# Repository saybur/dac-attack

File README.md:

DAC Attack!
===========

A small [S/PDIF](https://en.wikipedia.org/wiki/S/PDIF) to
[line-level](https://en.wikipedia.org/wiki/Line_level) audio adapter design.
The intended use case is with some versions of
[ZuluSCSI](https://zuluscsi.com/), though the design should work with any
S/PDIF compatible output source generating a TTL-compatible signal.

Used with a compatible board, and the appropriate firmware, this allows sending
audio to a retro computer. See later sections for usage information.

As of this writing, only some ZuluSCSI variants offer audio output. This list
may change in the future. Refer to the ZuluSCSI project page for details about
audio output support.

License and Disclaimer
----------------------

This project is made available under the CERN Open Hardware Licence
strongly-reciprocal variant version 2, available at [LICENSE](LICENSE).

This source is distributed WITHOUT ANY EXPRESS OR IMPLIED WARRANTY, INCLUDING
OF MERCHANTABILITY, SATISFACTORY QUALITY AND FITNESS FOR A PARTICULAR PURPOSE.
Please see the CERN-OHL-S v2 for applicable conditions.

ZuluSCSI&trade; is a registered trademark of Rabbit Hole Computing&trade;, used
with permission.

Assembly
--------

The author has had JLCPCB assemble these boards as prototypes. The files
`dac-attack-bom.csv` and `dac-attack-top-pos.csv` files were used successfully,
though caution should still be excercised: other open-source hardware projects
have reported some inconsistency in individual orders using files like these.

Adding through-hole components to assembled boards is relatively
straightforward. The choice of what connectors to solder is up to the user:

- 'analog' provides standard line-level output for sending to a sound card.
- 'digital' provides TTL-level S/PDIF from the CS8416 chip, which should
  _theoretically_ be suitable for sending to a sound card with a digital-in
  connector, ~~those this use case is NOT TESTED~~ florian3 on Vogons reports
  this is working fine, thanks for testing!
- 'ext button' provides a place to attach a button for the **B_READ** line.
- 'user' is connected to the U pin of the CS8416. This feature is not tested
  and this pad can be left vacant.
- The four pads for **G**, **3V**, **D_IN**, and **B_READ** are available if
  you do not want to use the modular connector. See the later section for
  hookup information.

Part numbers for through-hole parts are in [bom-full.csv](bom-full.csv).

Installation
------------

The screw holes on the board are spaced to match a 2.5" hard drive, which is
the same pattern on most ZuluSCSI boards. Use standoffs to prevent shorting
connections. An example mount is shown below. The full BOM has some options,
which you can probably also find at your local hardware store or a convenient
online retailer.

Most parent boards use either a 0.1" holes _or_ a matching 4-pin modular
connector. Instructions vary between these two board types.

__Important note:__ DAC Attack uses a 4-pin connector that matches common
hobbyist I2C formats; however, the board is __not compatible__ with I2C.

### 0.1 Connectors

**Carefully** solder a socket on the parent board. Most will need either a 2x2
or 1x4 connector for this. Example parts to order are in the BOM. You only need
to solder to points labeled **GND**, **3V0**, **SCL**, and **SDA** on the
bottom of the board. Again, use great care during this process to avoid
damaging anything.

Once soldered, connect a suitable cable from the socket to the DAC's modular
connector. Potential options are listed in the BOM. If the DAC's modular
connector is not populated, or you would prefer not to use it, the separate
labeled points on the DAC may be used instead.

If using the modular cable pin breakout version, colors should correspond as
follows:

- Black: GND
- Red: VCC (3V)
- Blue: B_READ ('SDA' label)
- Yellow: D_IN ('SCL' label)

### Modular Connector

If your parent board is equipped with a 1x4 modular connector, you're all set:
just connect the board to the DAC.

If the parent board does not have a modular connector, the most straightforward
option is to add the modular connector, likely part _BM04B-SRSS-TB(LF)(SN)_.

Cabling
-------

Once you have installed the board and applied correct firmware (if needed), all
that remains is connecting the 'analog' port to a suitable target. Most period-
correct sound cards will use either a 3-pin or 4-pin cable for connecting a CD
drive. This pinout is also compatible with the one used on retro Mac computers.

It is recommended to test your configuration to determine if stereo audio is
being handled appropriately. If it is not, rotate the cable in the socket.

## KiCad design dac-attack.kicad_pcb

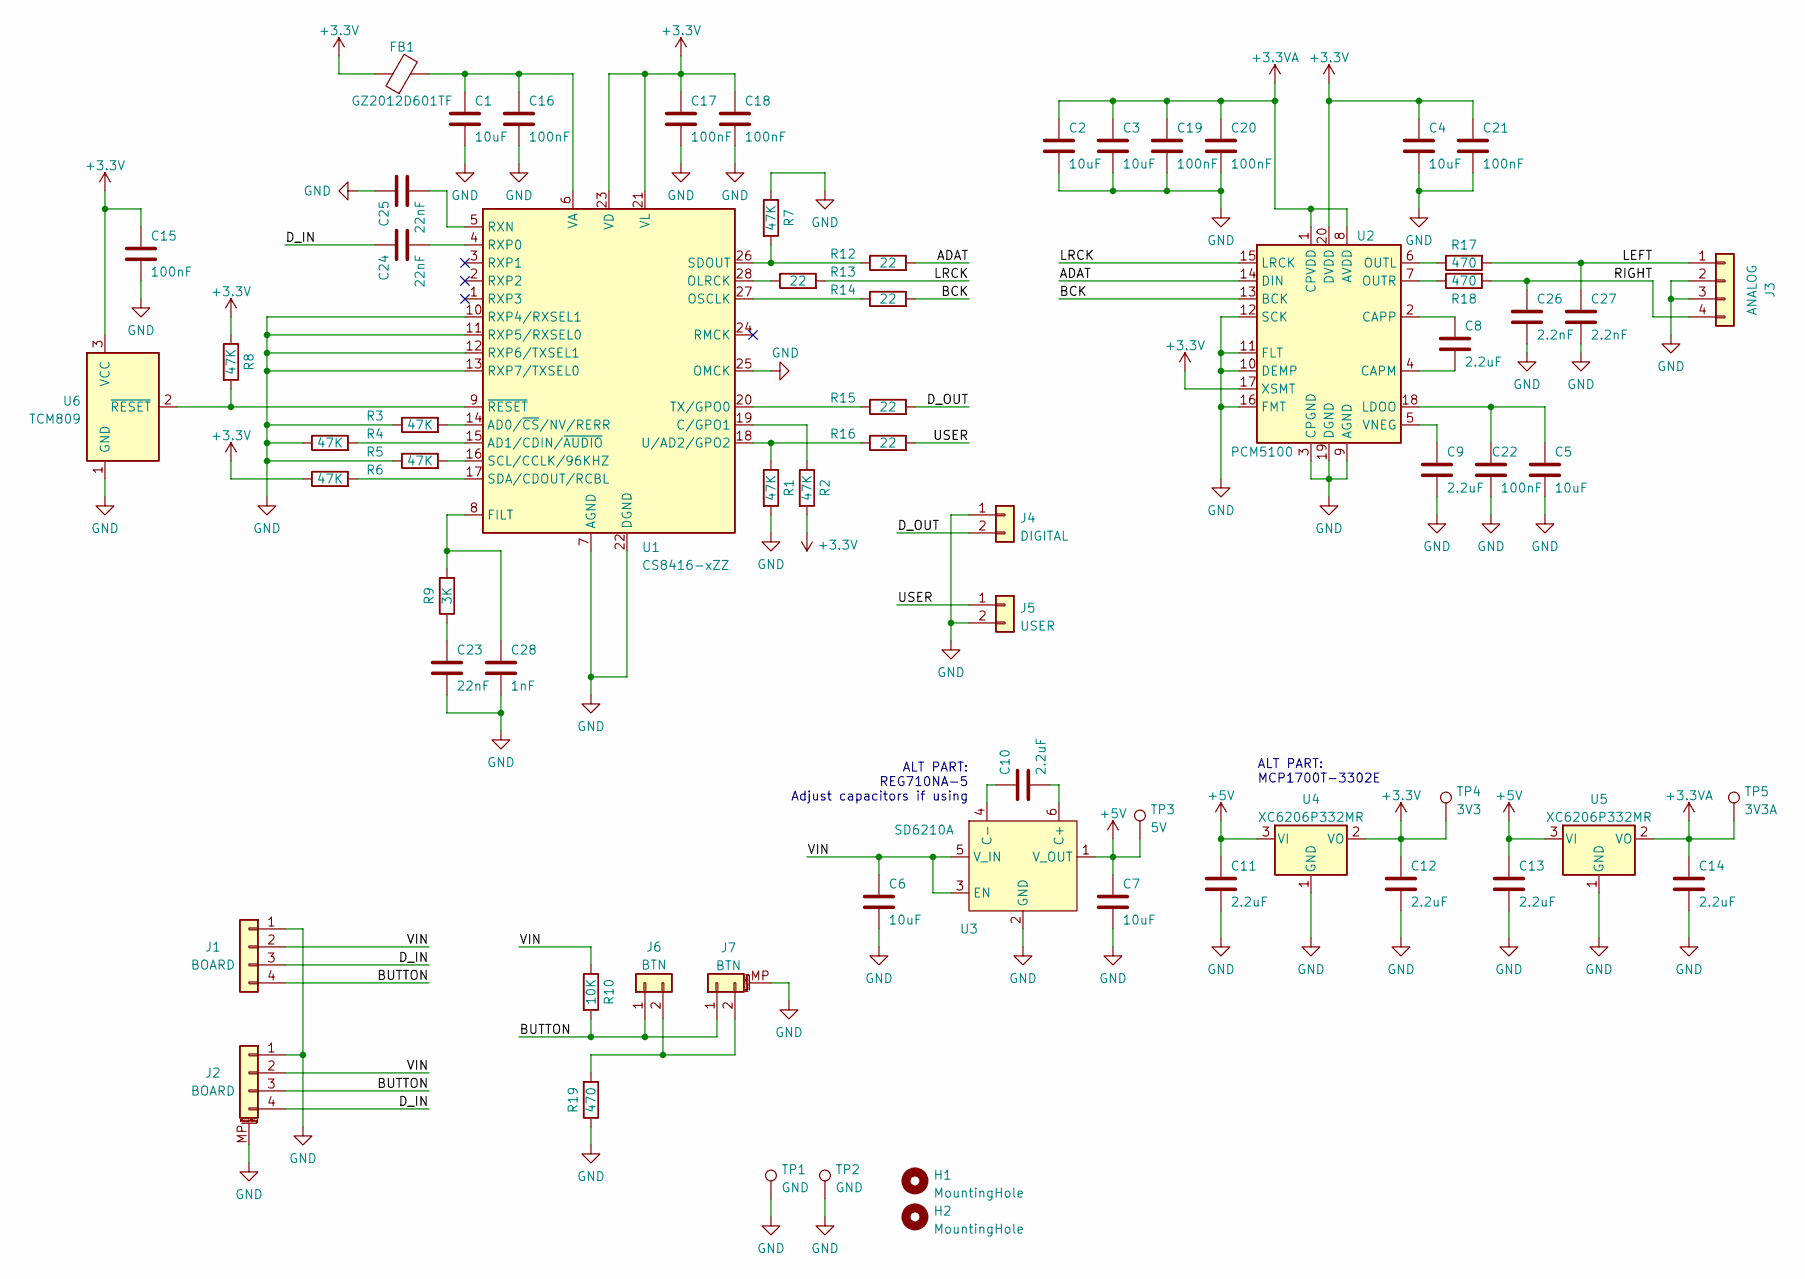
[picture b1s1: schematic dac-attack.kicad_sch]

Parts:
C1, C2, C3, C4, C5, C6, C7: 10uF; C_0603_1608Metric
C8, C9, C10, C11, C12, C13, C14: 2.2uF; C_0603_1608Metric
C15, C16, C17, C18, C19, C20, C21, C22: 100nF; C_0402_1005Metric
C23, C24, C25: 22nF; C_0402_1005Metric
C26, C27: 2.2nF; C_0805_2012Metric
C28: 1nF; C_0402_1005Metric
FB1: GZ2012D601TF; L_0805_2012Metric
H1, H2: MountingHole; MountingHole_3.2mm_M3
J1: BOARD; PinHeader_1x04_P2.54mm_Vertical
J2: BOARD; JST_SH_SM04B-SRSS-TB_1x04-1MP_P1.00mm_Horizontal
J3: ANALOG; 0705530003
J4: DIGITAL; 0705530001
J5: USER; PinHeader_1x02_P2.54mm_Vertical
J6: BTN; PinHeader_1x02_P2.54mm_Vertical
J7: BTN; JST_SH_SM02B-SRSS-TB_1x02-1MP_P1.00mm_Horizontal
R1, R2, R3, R4, R5, R6, R7, R8: 47K; R_0402_1005Metric
R9: 3K; R_0603_1608Metric
R10: 10K; R_0402_1005Metric
R12, R13, R14, R15, R16: 22; R_0402_1005Metric
R17, R18, R19: 470; R_0402_1005Metric
TP1, TP2: GND; TestPoint_Keystone_5000-5004_Miniature
TP3: 5V; TestPoint_Pad_D1.0mm
TP4: 3V3; TestPoint_Pad_D1.0mm
TP5: 3V3A; TestPoint_Pad_D1.0mm
U1: CS8416-xZZ; TSSOP-28_4.4x9.7mm_P0.65mm
U2: PCM5100; TSSOP-20_4.4x6.5mm_P0.65mm
U3: SD6210A; SOT-23-6
U4, U5: XC6206P332MR; SOT-23
U6: TCM809; SOT-23

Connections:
+3.3VA: C2.1, C3.1, C14.1, C19.1, C20.1, TP5.1, U2.1 (CPVDD), U2.8 (AVDD), U5.2 (VO)
+3V3: C4.1, C12.1, C15.1, C17.1, C18.1, C21.1, FB1.1, R2.2, R6.1, R8.1, TP4.1, U1.21 (VL), U1.23 (VD), U2.17 (XSMT), U2.20 (DVDD), U4.2 (VO), U6.3 (VCC)
+5V: C7.1, C11.1, C13.1, TP3.1, U3.1 (V_OUT), U4.3 (VI), U5.3 (VI)
/ADAT: R12.2, U2.14 (DIN)
/BCK: R14.2, U2.13 (BCK)
/BUTTON: J1.4, J2.3, J6.1, J7.1, R10.2
/D_IN: C24.1, J1.3, J2.4
/D_OUT: J4.2, R15.2
/LEFT: C27.1, J3.1, R17.2
/LRCK: R13.2, U2.15 (LRCK)
/RIGHT: C26.1, J3.4, R18.2
/USER: J5.1, R16.2
/VIN: C6.1, J1.2, J2.2, R10.1, U3.3 (EN), U3.5 (V_IN)
GND: C1.2, C2.2, C3.2, C4.2, C5.2, C6.2, C7.2, C9.2, C11.2, C12.2, C13.2, C14.2, C15.2, C16.2, C17.2, C18.2, C19.2, C20.2, C21.2, C22.2, C23.2, C25.1, C26.2, C27.2, C28.2, J1.1, J2.1, J2.MP (MountPin), J3.2, J3.3, J4.1, J5.2, J7.MP (MountPin), R1.2, R3.1, R4.1, R5.1, R7.1, R19.1, TP1.1, TP2.1, U1.7 (AGND), U1.10 (RXP4/RXSEL1), U1.11 (RXP5/RXSEL0), U1.12 (RXP6/TXSEL1), U1.13 (RXP7/TXSEL0), U1.22 (DGND), U1.25 (OMCK), U2.3 (CPGND), U2.9 (AGND), U2.10 (DEMP), U2.11 (FLT), U2.12 (SCK), U2.16 (FMT), U2.19 (DGND), U3.2 (GND), U4.1 (GND), U5.1 (GND), U6.1 (GND)
unnamed: C1.1, C16.1, FB1.2, U1.6 (VA)
unnamed: C8.1, U2.2 (CAPP)
unnamed: C8.2, U2.4 (CAPM)
unnamed: C9.1, U2.5 (VNEG)
unnamed: C10.1, U3.4 (C-)
unnamed: C10.2, U3.6 (C+)
unnamed: C5.1, C22.1, U2.18 (LDOO)
unnamed: C23.1, R9.1
unnamed: C24.2, U1.4 (RXP0)
unnamed: C25.2, U1.5 (RXN)
unnamed: C28.1, R9.2, U1.8 (FILT)
unnamed: J6.2, J7.2, R19.2
unnamed: R1.1, R16.1, U1.18 (U/AD2/GPO2)
unnamed: R2.1, U1.19 (C/GPO1)
unnamed: R3.2, U1.14 (AD0/~CS/NV/RERR)
unnamed: R4.2, U1.15 (AD1/CDIN/~AUDIO)
unnamed: R5.2, U1.16 (SCL/CCLK/96KHZ)
unnamed: R6.2, U1.17 (SDA/CDOUT/RCBL)
unnamed: R8.2, U1.9 (~RESET), U6.2 (~RESET)
unnamed: R7.2, R12.1, U1.26 (SDOUT)
unnamed: R13.1, U1.28 (OLRCK)
unnamed: R14.1, U1.27 (OSCLK)
unnamed: R15.1, U1.20 (TX/GPO0)
unnamed: R17.1, U2.6 (OUTL)
unnamed: R18.1, U2.7 (OUTR)

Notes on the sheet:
ALT PART: MCP1700T-3302E
ALT PART: REG710NA-5 Adjust capacitors if using

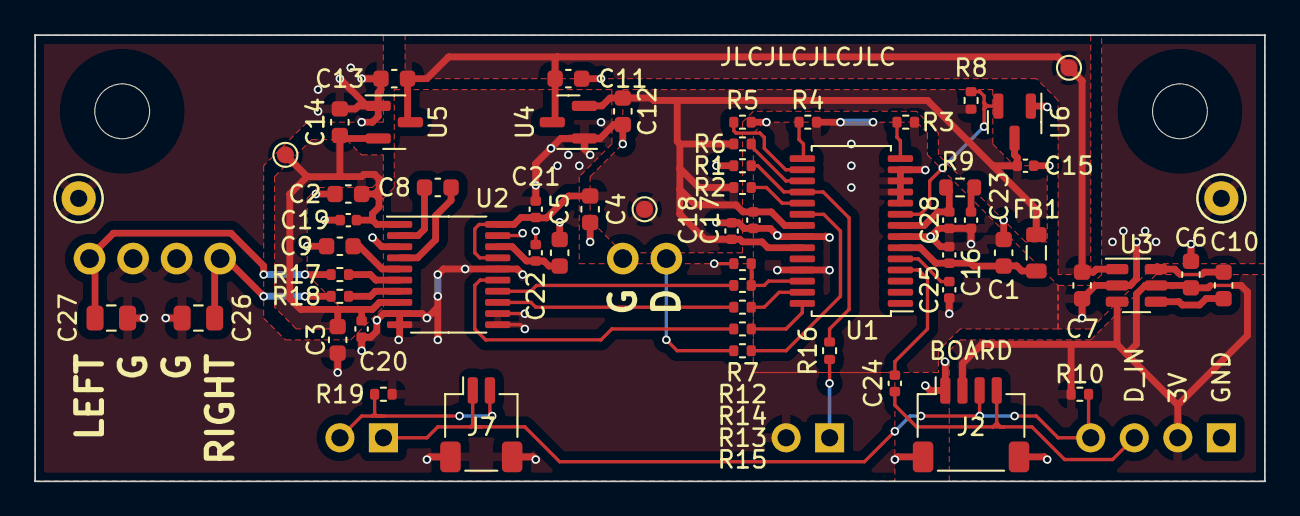
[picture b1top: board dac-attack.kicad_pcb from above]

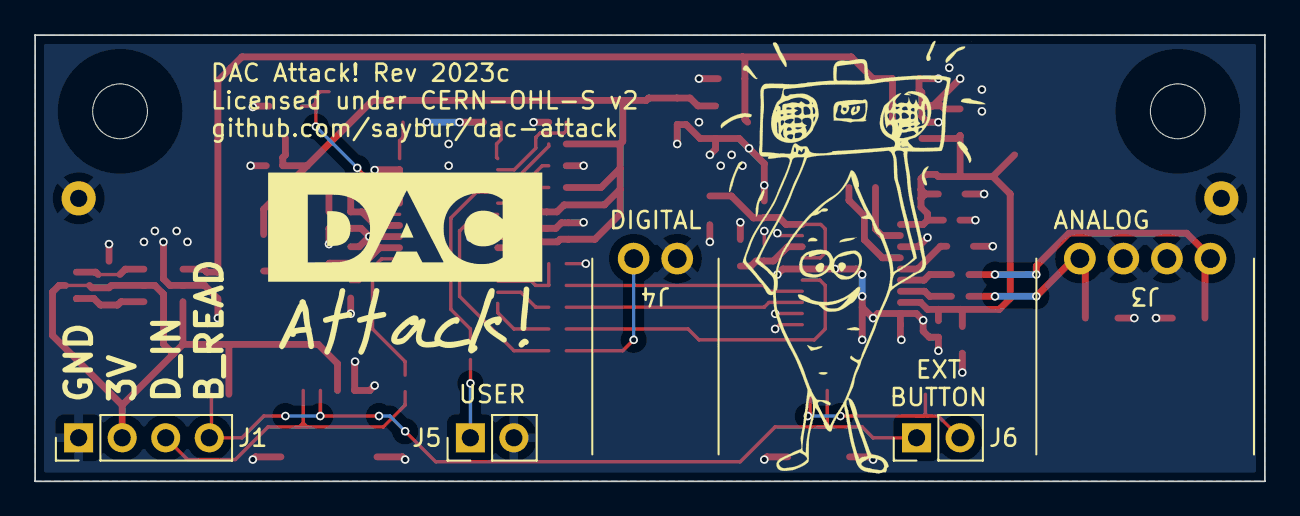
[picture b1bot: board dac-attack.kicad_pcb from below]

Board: 2 copper layers, 71.8 x 26.0 mm, 67 parts (5 on the bottom side), 39 nets.

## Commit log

2023-04-27 LICENSE and initial README upload.
2023-04-27 Initial design.
2023-04-27 Added a note about project status.
2023-05-09 Initial work on revision 2023b.
2023-05-14 Tweaks to 2023b
    Fixed one net, widened traces, made some minor silkscreen changes.
2023-05-14 Added missing BOM / positioning files.
2023-05-24 Board revision 2023c.
    No component layout changes, just minor tweaks to mounting holes and silkscreening.
2023-05-24 Add J2 to manufacturing and list some parts for TH pins.
2023-05-24 Include a CHANGES file per license recommendation.
2023-05-24 Added some optional BOM components.
2023-05-24 Include a user guide for the license.
2023-05-24 Add more README detail, including some usage instructions.
2023-05-24 Fix typo in README.
2023-06-13 Added note about compatibility with some board revisions.

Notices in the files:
dac-attack.kicad_pcb:
Licensed under CERN-OHL-S v2
